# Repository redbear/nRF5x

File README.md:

# nRF5x

This repository contains the resources for the RedBear nRF5x BLE development board.

BLE Nano and RBL_nRF51822
* [nRF51822](./nRF51822)

BLE Nano 2 and Blend 2
* [nRF52832](./nRF52832)

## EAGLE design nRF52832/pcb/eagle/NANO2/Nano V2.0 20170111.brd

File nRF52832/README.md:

# nRF5x

Thank you for supporting [RedBear nRF52832 Kickstarter](https://www.kickstarter.com/projects/redbearinc/bluetooth-5-ready-ble-module-nano-2-and-blend-2) campaign.

Currently, this repository is for nRF52832 based boards, we will merge nRF51 to this later.

## nRF52832

The nRF52832 BLE SoC combines its ARM processor with a 2.4GHz multiprotocol radio featuring -96 dB RX sensitivity, 512 kB Flash memory, 64 kB RAM and NFC-A tag for “Touch-to-Pair” capability. You can read all [nRF52832 advanced features](https://www.nordicsemi.com/eng/Products/Bluetooth-low-energy/nRF52832) on Nordic's website.

### nRF52 vs nRF51

The nRF51822 runs at 16 MHz only, it is only a Cortex-M0 MCU without DSP and FPU for complicated applications. You will not be able to develop Apple HomeKit projects using nRF51.

## BLE Module (MB-N2)

At the heart of all the new products is our new BLE Module model# MB-N2. It houses the Nordic nRF52832, an on-board antenna and other components special tuning for great performance and low power consumption.

The module provides all GPIO pins and supports all advance features offer by Nordic nRF52832.

With your support, we have our module certified for CE, FCC and Bluetooth. If you use this module for your own products, not only you have the assurance, you will also save some cost on your own product certifications.

Bluetooth QDID: [91904](https://www.bluetooth.org/tpg/QLI_viewQDL.cfm?qid=33543)

If you have some great project ideas, please refer to the [datasheet](./datasheet/MB-N2 Datasheet.pdf) of the module MB-N2 for details.

## BLE Nano 2

We launched our first BLE Nano in 2014 and it is our most popular product. We design Nano 2 as a ‘drop-in’ replacement, with exactly the same form factor, and in most instances only need to change few firmware code. In addition, the new development board also offers a U.FL connector for an external NFC antenna, while users will benefit from the extra processing power and hardware resources of the nRF52832 SoC.

### DAPLink

This board has an ARM Cortex-M3 MCU and is used to program and debug an application running on Nano 2 via SWD. DAPLink is an open source project by ARM mbed team, more about [DAPLink](https://developer.mbed.org/handbook/DAPLink).

### Proto Board

We design this new Proto Board for you to get started easily. You can power your Nano via coin cell battery, rechargeable battery or USB. The top part could be removed if you don't need it. It has 3 connectors for Seeed's Grove modules (more details below). Last but not least, we have reserved a place for the Apple MFi authentication coprocessor; you can develop BLE HomeKit product if you have the MFi license. 

## Blend 2

Our Blend is very popular as it is a "full-size" Arduino compatible board which supports most shields. It has on board a Cortex-M3 MCU that supports DAPLink, slot for Apple MFi coprocessor and two Grove connectors.

You should choose the Blend 2 if you want to test all GPIOs and functions available on the Nordic nRF52832 SoC. 

## Getting Started

Before starting to use the nRF52832 boards, you need to do some preparations.

* [Out-of-Box Test](./docs/Getting_Started_Guide.md) will guide you to test the nRF52 board.
  
* [Updating the DAPLink interface firmware](./daplink) to the latest version, otherwise, you may have problem for drag-n-drop programming the nRF52 SoC.

* [Installing nRF52832 board package](./docs/Arduino_Board_Package_Installation_Guide.md) for using the Arduino IDE for development your projects.

## Technical Support

* If you think you have a **faulty unit**, kindly [open a support ticket](https://redbear.freshdesk.com/) and the support team will follow up with you.

* For software issues, please submit in this repository.

* [RedBear Discuss Forum](http://discuss.redbear.cc)

* [Nordic Forum](https://devzone.nordicsemi.com/questions/)

## Resoureces

* [Documentations](./docs)
	* [Product Specifications](./docs/Specifications.md)
	* [Getting Started Guide](./docs/Getting_Started_Guide.md)
* [Nordic nRF52832 Product Specification](http://infocenter.nordicsemi.com/index.jsp?topic=%2Fcom.nordic.infocenter.nrf52%2Fdita%2Fnrf52%2Fchips%2Fnrf52832_ps.html)
* [MB-N2 Datasheet](./datasheet/MB-N2%20Datasheet.pdf)
* [PCB Files](./pcb)

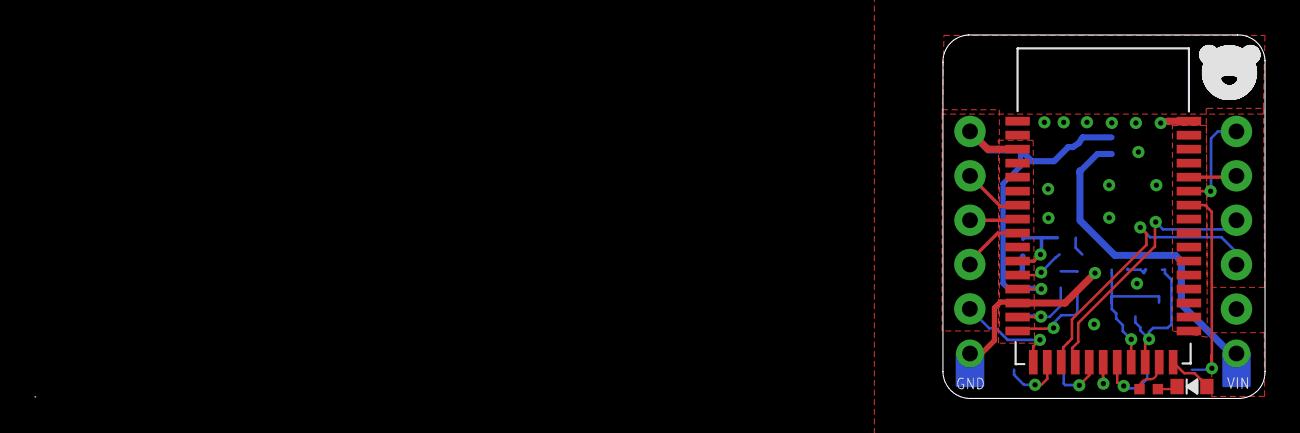
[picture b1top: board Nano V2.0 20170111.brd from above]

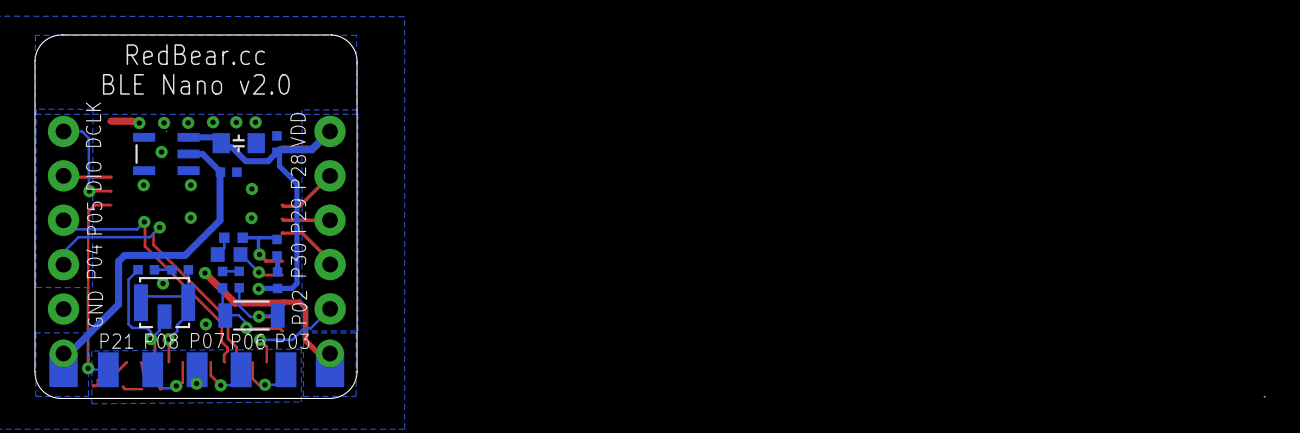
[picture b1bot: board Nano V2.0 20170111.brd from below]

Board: 2 copper layers, 70.3 x 20.8 mm, 34 parts (20 on the bottom side), 25 nets.

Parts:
1: TPDOT_1; DOT_1
CAP1: 1UF; C-0402
CAP5, CAP9, CAP10: 0.1UF; C-0402
CAP6, CAP7: 12PF; C-0402
CAP8: 22uf; C0805
CAP24, CAP26: NC; C-0402
GND1: TPDOT_1.5; DOT_1.5
L3: 10UH; R0603
L5: 15NH; R0402
LED2: yellow; LED0603
P02, P04, P05, P29, P30: TPDOT_1.5; DOT_1.5
P03, P06, P07, P08: 1P
P28: TPTPEB; TPEB
R2: 4.7K; R0402
RESET: 1P
RF-CON: NFC; IPEX
SCLK: TPDOT_1.5; DOT_1.5
SDIO: TPDOT_1.5; DOT_1.5
U1: TLV70433TLV70433; SOT-23-5
U$1: RBT07
VDD: TPTPEB; TPEB
VIN: TPDOT_1; DOT_1
Y1: 32.768KHZ; CRY_3215

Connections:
GND: 1.1, CAP1.1, CAP5.2, CAP6.1, CAP7.2, CAP8.1, CAP9.1, CAP10.2, CAP24.2, CAP26.2, GND1.1, R2.1, U1.1, U$1.1, U$1.2, U$1.14, U$1.26, U$1.43
unnamed: P30.1, U$1.9
unnamed: L3.2, U$1.12
unnamed: L3.1, L5.2
unnamed: SDIO.1, U$1.39
unnamed: CAP1.2, L5.1, U$1.11
unnamed: SCLK.1, U$1.38
unnamed: CAP6.2, U$1.15, Y1.2
unnamed: P03.P$1, U$1.18
unnamed: RESET.P$1, U$1.37
unnamed: P04.1, U$1.19
unnamed: P05.1, U$1.20
unnamed: P06.P$1, U$1.21
unnamed: LED2.2, R2.2
unnamed: P02.1, U$1.17
unnamed: P29.1, U$1.8
unnamed: P28.1, U$1.7
unnamed: CAP7.1, U$1.16, Y1.1
unnamed: P07.P$1, U$1.22
unnamed: P08.P$1, U$1.23
unnamed: CAP10.1, U1.2, VIN.1
P09: CAP26.1, RF-CON.2, RF-CON.3, U$1.24
P10: CAP24.1, RF-CON.1, U$1.25
P11: LED2.1, U$1.27
VCC: CAP5.1, CAP8.2, CAP9.2, U1.3, U$1.3, U$1.13, VDD.1

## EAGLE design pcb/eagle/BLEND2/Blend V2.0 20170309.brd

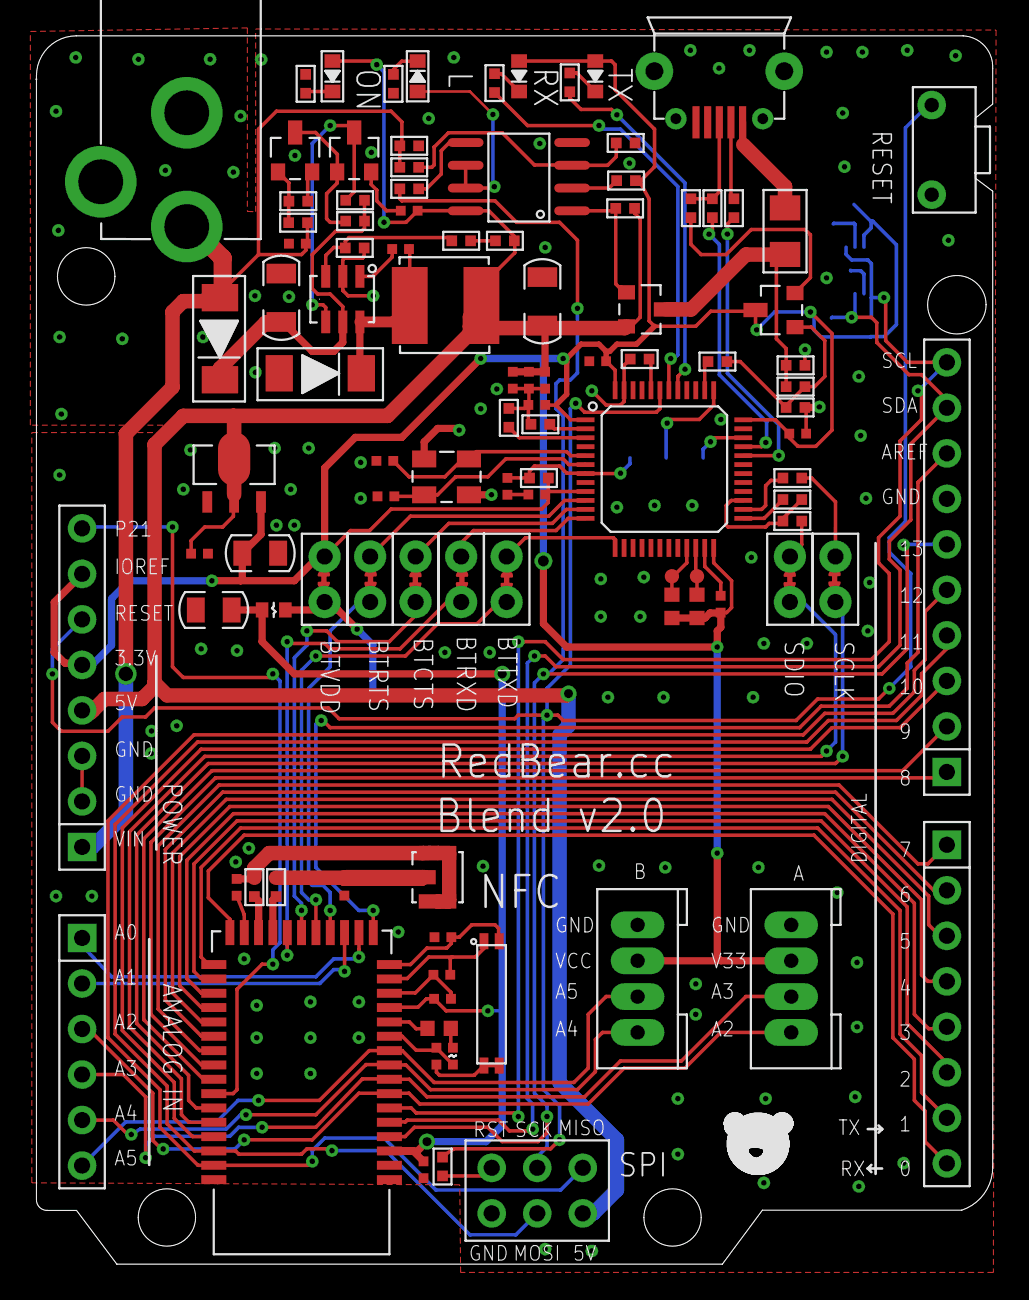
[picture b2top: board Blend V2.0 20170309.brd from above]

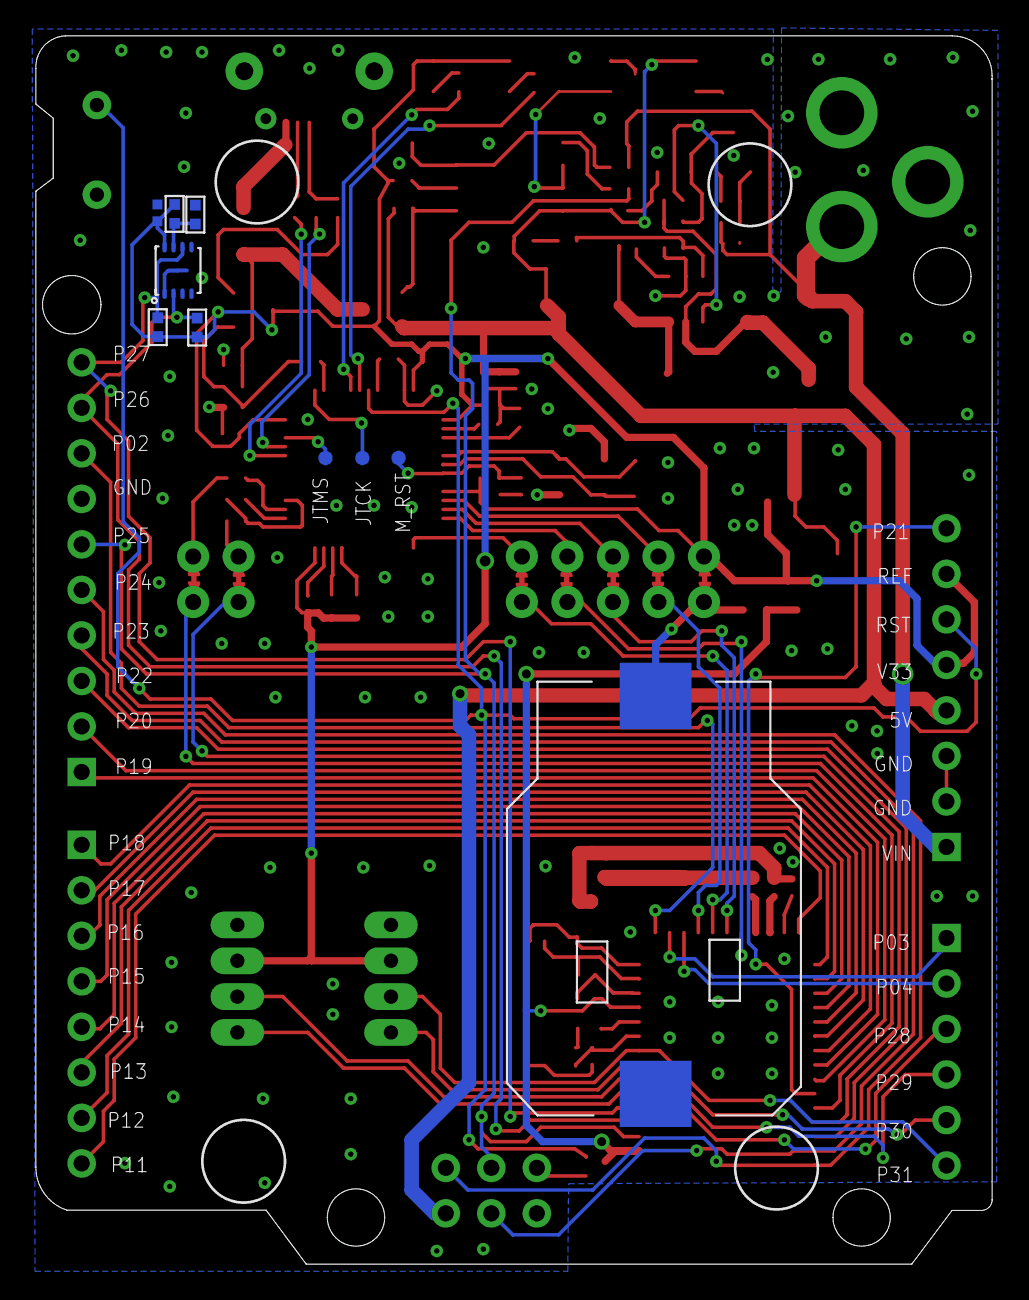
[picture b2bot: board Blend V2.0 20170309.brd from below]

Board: 2 copper layers, 53.4 x 68.5 mm, 121 parts (10 on the bottom side), 93 nets.

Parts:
A: SIP-42.0; CONETER-4-2.0
B: SIP-42.0; CONETER-4-2.0
BAT: BAT
BT-VDD: SIP-22.54; SIP-2
C1, C26: 1uF; C-0402
C2, C7, C8, C13, C14, C15, C16, C17, C20, C24, C25: 0.1uF; C-0402
C3, C4: 15p; C-0402
C5, C6: nc; C-0402
C9: 4.7uF; C-0402
C10: 10uF; C0805
C11, C12: 20p; C-0402
C18: 47uF; C1206
C19: 10nF; C-0402
C21: 100pF; C-0402
C22: 33pF; C-0402
C23: 22uF; C0805
C41: 10uF; C1206
D1: LAN; LED-0603
D3: IN5819; D-1810
D4: green; LED-0603
HEAD-2*1: HEAD-23; PAIZHEN3X2PIN2.54
IN5819: D2; D-1810
J5: DC-JACK-3P; DC-005
J6, J9: SIP-8SIP-8AA; PAIZHEN8P_2.54AA
J7: SIP-6SIP-6AA; PAIZHEN6P_2.54AA
J8: SIP-1010P_2.54A; PAIZHEN10P-2.54A
JTCK: TPTP; TP
JTMS: TPTP; TP
K-1: K-1811; K2-1101F
L1: 10uH; R0603
L2: 15nH; R-0402S
L3: 4.7UH; L4X4
L20: 10uH; R-0603A
MP2359: MP2359
M_RST: TPTP; TP
NFC: IPEXIPEX; IPEX
NMOS2: Q2; SOT-23
NMOS3: Q1; SOT-23
Q4: N-MOS; SOT-23
Q7: PMOS; SOT-23
R1, R3, R30, R37: 0R; R0402
R2, R4: 4.7K NC; R0402
R5, R6: NC; R0402
R7, R9, R15, R16: 10k; R0402
R8: nc; R0402
R10, R11: NC; R0603
R12, R13, R14, R23: 100R; R0402
R17: 4.7k; R0402
R18: 1.5K; R0402
R19, R20, R34, R39: 33R; R0402
R21, R26, R33, R35, R36, R38: 10K; R0402
R22: 36K; R0402
R24, R28, R29: 100K; R0402
R25: 11K; R0402
R27: 2.7K; R0402
R31: 49.9K; R0402
R32: 9.53K; R0402
R40: 4.7K; R0402
RES1: 500mA fuse; R1206A
RX: GREEN; LED0603
S1, S2, S3, S4, S5, S6: SIP-22.54; SIP-2
S55: TP_OPEN
T1, T2, T3, T4, T5, T6: TP_OPEN
TP1, TP2: TPTP; TP
TX: BLUE; LED0603
U1: STM32F103LQFP48; LQFP-48-7X7
U11: MB-N2; RBT07
U$2: CRY_7015; CRY_7015_SMT
U$3: APPLE_ICUSON8A; USON8_A
U$15: MICRO_USBMICRO_USB; MICRO_USB
U$16: XC6203SOT89; SOT-89
U$19: SGM358; SOP-8
Y1: 16MH; CRY_3225_SMT

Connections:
+3V3: A.3, B.3, BT-VDD.2, C8.2, C9.2, C10.1, C14.1, C15.2, C16.1, C25.1, J9.5, J9.7, Q4.3, R2.2, R4.2, R5.2, R9.2, R10.1, R11.1, R34.1, RX.1, S55.P$2, TX.1, U1.1, U1.9, U1.24, U1.36, U1.48, U$3.8, U$16.3
+5V: C17.1, C18.2, C20.2, C21.2, C22.2, C26.2, D4.1, HEAD-2*1.3, J9.4, L3.P$2, Q7.2, R24.2, R30.1, U$16.2, U$19.8
AGND: A.4, B.4, BAT.P$2, C1.1, C2.2, C3.1, C4.2, C5.1, C6.2, C7.2, C8.1, C9.1, C10.2, C11.2, C12.1, C13.1, C14.2, C15.1, C16.2, C17.2, C18.1, C20.1, C21.1, C22.1, C23.2, C24.1, C25.2, C26.1, C41.2, D3.1, HEAD-2*1.1, J5.P$2, J5.P$3, J8.7, J9.2, J9.3, K-1.2, MP2359.2, NMOS2.2, NMOS3.2, R6.1, R7.1, R8.1, R17.2, R22.1, R26.2, R27.2, R32.2, R33.2, R36.1, R38.1, R40.1, U1.8, U1.23, U1.35, U1.47, U11.1, U11.2, U11.14, U11.26, U11.43, U$2.2, U$2.3, U$3.1, U$3.9, U$15.4, U$15.5, U$15.6, U$15.7, U$15.8, U$15.9, U$16.1, U$19.4, Y1.2, Y1.4
CTS/P07: S2.1, T2.P$2, U11.22
DN: R20.2, U1.32
DP: R19.2, U1.33
M/RST: C13.2, M_RST.P$1, R9.1, U1.7
MP2359: C19.1, MP2359.1
unnamed: L1.1, L2.2
unnamed: L1.2, U11.12
unnamed: C1.2, L2.1, U11.11
unnamed: C3.2, U11.15, U$2.1
unnamed: C4.1, U11.16, U$2.4
unnamed: C5.2, NFC.2, NFC.3, R3.2
unnamed: C6.1, NFC.1, R1.2
unnamed: R10.2, TP1.P$1, U1.21
unnamed: R5.1, R6.2, U$3.7
unnamed: C11.1, U1.5, Y1.3
unnamed: R7.2, U1.2
unnamed: R8.2, U1.3
unnamed: C12.2, U1.6, Y1.1
unnamed: R11.2, TP2.P$1, U1.22
unnamed: Q4.2, R18.2
unnamed: Q4.1, R21.1, R22.2, R23.1
unnamed: S4.2, T4.P$1, U1.13
unnamed: R18.1, R19.1, U$15.3
unnamed: R14.2, U1.25
unnamed: R15.1, U1.41
unnamed: R16.1, U1.42
unnamed: R20.1, U$15.2
unnamed: R17.1, U1.44
unnamed: BAT.P$1, BT-VDD.1, L20.2, S55.P$1
unnamed: NMOS3.1, R25.2, R27.1
unnamed: RES1.1, U$15.1
unnamed: NMOS2.1, NMOS3.3, R28.2
unnamed: R34.2, U$19.2
unnamed: R35.2, R36.2, U$19.3
unnamed: D4.2, R33.1
unnamed: MP2359.4, NMOS2.3, R29.2
unnamed: D1.1, U$19.6, U$19.7
unnamed: MP2359.3, R31.2, R32.1
unnamed: R30.2, R31.1
unnamed: D1.2, R38.2
unnamed: C19.2, D3.2, L3.P$1, MP2359.6
unnamed: R37.2, U$19.5
unnamed: HEAD-2*1.6, R39.2
P02_AREF: J8.8, U11.17
P03_A0: J7.1, U11.18
P04_A1: J7.2, U11.19
P09: R1.1, U11.24
P10: R3.1, U11.25
P11_D0/RX: J6.8, U11.27
P12_D1/TX: J6.7, U11.28
P13_D2/SDA: J6.6, U11.29
P14_D3/SCL: J6.5, U11.30
P15_D4: J6.4, U11.31
P16_D5: J6.3, U11.32
P17_D6: J6.2, U11.33
P18_D7: J6.1, U11.34
P19_D8: J8.1, U11.35
P20_D9: J8.2, U11.36
P21: J9.8, U11.37
P22_D10: J8.3, U11.40
P23_D11: HEAD-2*1.2, J8.4, U11.41
P24_D12: HEAD-2*1.4, J8.5, U11.42
P25_D13: HEAD-2*1.5, J8.6, R37.1, U11.4
P26_SDA1: J8.9, R2.1, U11.5, U$3.2
P27_SCL1: J8.10, R4.1, U11.6, U$3.6
P28_A2: A.1, J7.3, U11.7
P29_A3: A.2, J7.4, U11.8
P30_A4: B.1, J7.5, U11.9
P31_A5: B.2, J7.6, U11.10
PA0: S1.2, T1.P$1, U1.10
PA1: S2.2, T2.P$1, U1.11
PA2: S3.2, T3.P$1, U1.12
RESET: J9.6, K-1.1, R39.1, U1.43
RTS/P05: S1.1, T1.P$2, U11.20
RX: R16.2, RX.2
RXD/P08: S3.1, T3.P$2, U11.23
SCLK: R13.1, S5.1, S5.2, T5.P$1, T5.P$2, U11.38
SDIO: R12.1, S6.1, S6.2, T6.P$1, T6.P$2, U11.39
STM_JTCK: JTCK.P$1, U1.37
STM_JTMS: JTMS.P$1, U1.34
SWDCLK: R13.2, U1.26
SWDIO: R12.2, R14.1, U1.27
TX: R15.2, TX.2
TXD/P06: S4.1, T4.P$2, U11.21
USB5V: Q7.3, R21.2, R40.2, RES1.2
USBPON: Q7.1, R24.1, U$19.1
USB_RENUMN: R23.2, U1.38
VDD: C2.1, C7.1, C23.1, L20.1, U11.3, U11.13
VIN: C24.2, IN5819.1, J5.P$1, J9.1, R25.1, R26.1, R35.1
VIN+: C41.1, IN5819.2, MP2359.5, R28.1, R29.1

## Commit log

2017-01-21 nRF52 Public Release (Beta).
2017-02-22 Add MK20_V1.0 interface firmware for target nRF52832.
2017-03-08 Adds the missing firmware for erasing the whole chip.
2017-03-14 Add RBL_nRF51822
2017-03-21 Fix some format issues with README.MD.
2017-03-22 Modify README.md.
2017-03-23 Add DAPLink firmware of nRF5x.
2017-05-31 Adds the Nano ProtoBoard schematic.
2017-05-31 Adds PCB files in EAGLE format.
2017-06-09 Adds power supply notes.
2017-06-23 Add Mbed_Eddystone_User_Guide.md
2017-06-23 Change Mbed_Eddystone_User_Guide.md
2017-06-27 Adds the FCC/CE certification documents.
2017-07-10 Update BLEController.
2017-08-09 Fix minor issues in README.md
2017-10-20 Fixes for overflow of rtc in us_ticker
    There are 3 areas of changes for the rtc (real time clock). The first 2
    are actual fixes, the third is mostly a reorganization.
    1. The new version of the routine common_rtc_64bit_ticks_get() ensures that
    the full value of the rtc (56 bits from overflow and hw counter) are
    read correctly whether called from an interrupt or not. The old code
    simply added the overflows but this is unsafe since the hardware
2017-10-21 Fix for setting rtc compare when timeout just occurred.
    In us_ticker.c, need to make sure that we are not messing up the compare
    register calculation when the timeout just occurred. In previous code,
    could add 2^32 before calculating the rtc compare register when the
    timeout occurred. That results in the compare register set to 199
    seconds late. In the fix, just force rtc to expire as soon as
    possible.
2017-11-29 Add link to Mbed IDE user guide to README
2018-03-15 Add I2C_Guide.md
2018-03-27 better I2C_Guide and picture
2018-03-27 add for printing data to write and read reganding to flash
2018-07-05 Add files via upload
    BLE Nano v1.5 gerber file
2018-11-14 added generic nrf51/52 boards
2018-11-14 generic nrf51/52 boards mapped now to nano/nano2 variants
2018-11-14 added docs
